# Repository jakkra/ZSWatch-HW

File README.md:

# ZSWatch Hardware

> [!NOTE]
> This is the release branch with tested PCB files.<br>
> For hardware development branch go to [ZSWatch-HW/tree/2.0.6_Dev](https://github.com/jakkra/ZSWatch-HW/tree/2.0.6_Dev).<br>
> For production files pick the [latest run here](https://github.com/jakkra/ZSWatch-HW/actions?query=event%3Apull_request_target) and scroll down to artifacts and pick `Watch`<br>
> Although tested, there may still be unknown issues not yet discovered and ordering ZSWatch PCBs are on your own risk.

## Table of Content

- [ZSWatch Hardware](#zswatch-hardware)
  - [Table of Contents](#table-of-contents)
  - [About](#about)
  - [Dock connector](#dock-connector)
  - [Directory structure](#directory-structure)
  - [Purchasing](#purchasing)
  - [Maintainer](#maintainer)

## About

Hardware repository for the [ZSWatch](https://github.com/jakkra/ZSWatch).

Please check the [wiki](https://github.com/jakkra/ZSWatch/wiki) for more information about the project.

## Dock connector

The pinout for the dock connector is shown below.

<table class="tg">
<thead>
  <tr>
    <th class="tg-0pky"></th>
    <th class="tg-0pky">Pin</th>
    <th class="tg-0pky">Description</th>
  </tr>
</thead>
<tbody>
  <tr>
    <td class="tg-0pky" rowspan="5"></td>
    <td class="tg-0pky">1</td>
    <td class="tg-0pky">VBUS (+5 V)</td>
  </tr>
  <tr>
    <td class="tg-0pky">2</td>
    <td class="tg-0pky">GND</td>
  </tr>
  <tr>
    <td class="tg-0pky">3</td>
    <td class="tg-0pky">SEL</td>
  </tr>
  <tr>
    <td class="tg-0lax">4</td>
    <td class="tg-0lax">D- / SWDIO</td>
  </tr>
  <tr>
    <td class="tg-0lax">5</td>
    <td class="tg-0lax">D+ / SWDCLK</td>
  </tr>
</tbody>
</table>

| SEL  | Function       |
|------|----------------|
|`LOW` | USB            |
|`HIGH`| SWD (Default)  |

## Directory structure

- `cad`: 3D model of the complete PCB
- `docs`: All kinds of project documentation like schematics, BOM, etc.
  - `drawings`: 2D drawings for subcomponents, etc.
  - `images`
- `project`: KiCad project for the PCB

## Purchasing

Please open `ZSWatch-navigate.html` and use the files listed under `purchasing` for ordering a PCB.

## Maintainer

- [Daniel Kampert](mailto:daniel.kameprt@kampis-elektroecke.de)
- [Jakob Krantz](mail@jakobkrantz.se)

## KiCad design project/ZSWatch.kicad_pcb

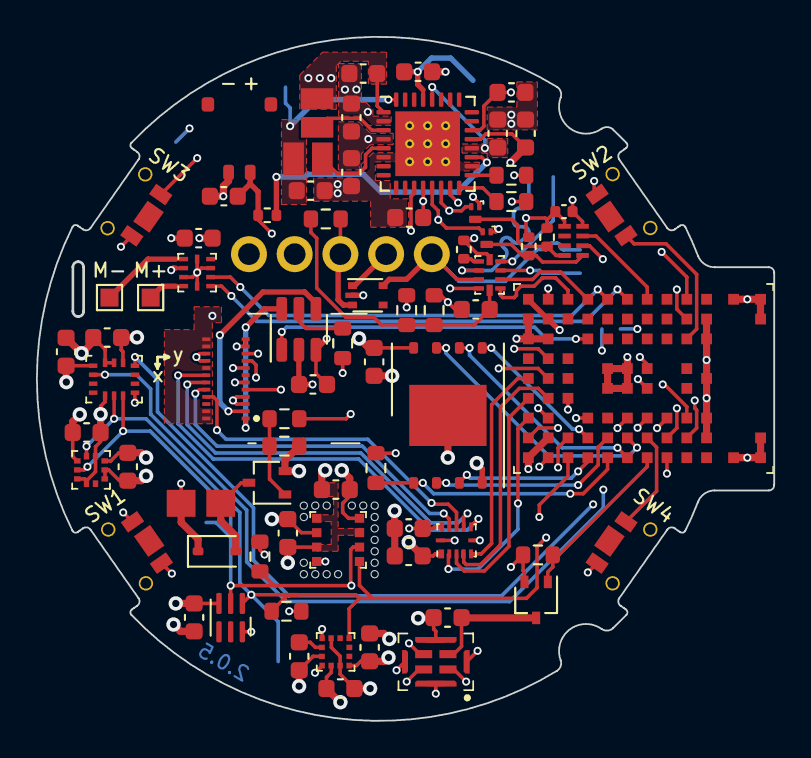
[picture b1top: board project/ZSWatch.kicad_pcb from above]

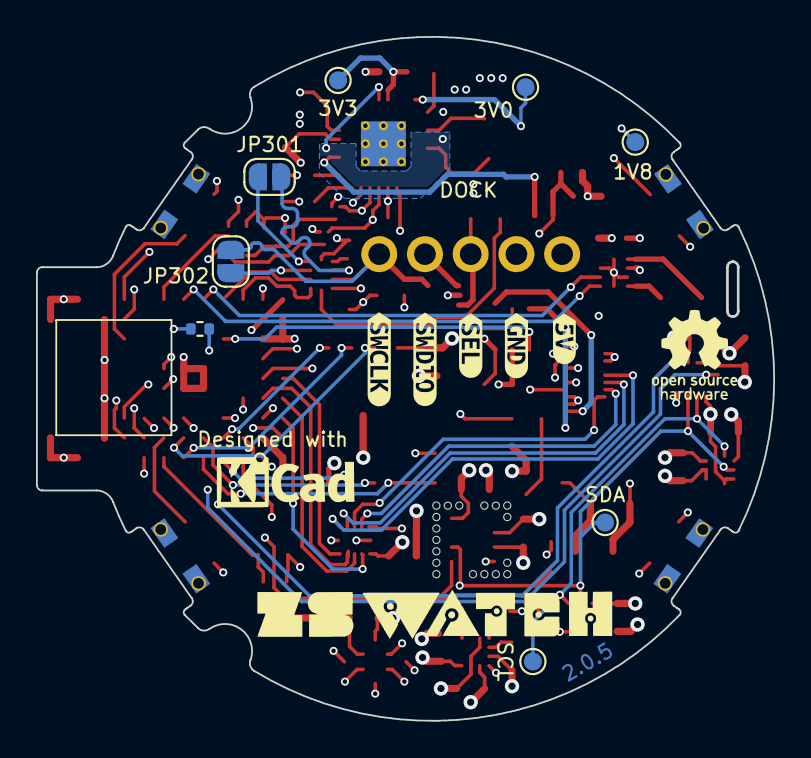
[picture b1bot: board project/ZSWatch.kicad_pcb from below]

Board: 4 copper layers, 41.0 x 38.0 mm, 89 parts (14 on the bottom side), 72 nets.

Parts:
BZ301: Buzzer; CMT-322-65-SMT-TR
C101, C110, C301: 1u; C_0603_1608Metric
C102, C201, C202, C203, C204, C206, C207, C210, C211, C212, C302, C303, C304, C305, C306: 100n; C_0603_1608Metric
C103: 2u2; C_0603_1608Metric
C104, C105, C106, C107, C108, C109, C209: 10u; C_0603_1608Metric
C208: 220n; C_0603_1608Metric
C307: 100n; C_0402_1005Metric
D301: BAS316; D_SOD-323
IC101: nPM1300-QEXX; QFN-32-1EP_5x5mm_P0.5mm_EP3.6x3.6mm_ThermalVias
IC201: APDS-9306-065; Broadcom_DFN-6_2x2mm_P0.65mm
IC202: BMI270; Bosch_LGA-14_3x2.5mm_P0.5mm_LayoutBorder3x4y
IC203: BMP581; Bosch_LGA-10_2x2mm_P0.5mm_ClockwisePinNumbering
IC204: LIS2MDLTR; LGA-12_2x2mm_P0.5mm
IC205: BME688; Bosch_LGA-8_3x3mm_P0.8mm_ClockwisePinNumbering
IC301: ESDALC6V1W5; SOT-665
IC302: FAN5622SX; TSOT-23-6
IC303: MX25U51245GZ4I00; WSON-8-1EP_8x6mm_P1.27mm_EP3.4x4.3mm
IC304: TS3USB221A; UQFN-10_1.55x2.05mm_P0.5mm
IC305: NTS0104GU12; XQFN-12-1.7x2mm_P0.4mm
IC306: DRV2603RUNT; WQFN-10_2x2mm_P0.5mm
IC307: RV-8263-C8
JP301, JP302: SolderJumper-2_P1.3mm_Open_RoundedPad1.0x1.5mm
L101, L102: 2u2; L_0806_2016
M301: NORA-B106
MK201: SPK0641HT4H-1
Q201: DMG1013UW-7; SOT-323_SC-70
Q301: BC817W; SOT-323_SC-70
Q302, Q303: PMZ550UNEYL; SOT-883
R101: 47k; R_0603_1608Metric
R102, R201, R307: 150k; R_0603_1608Metric
R103, R306, R310: 0R; R_0402_1005Metric
R301: 12k; R_0603_1608Metric
R302, R305: 100k; R_0603_1608Metric
R303, R304: 4k7; R_0603_1608Metric
R308: 270R; R_0603_1608Metric
R309, R313: 4k7; R_0402_1005Metric
R311: 180R; R_0603_1608Metric
R312: 100R; R_0603_1608Metric
S301: SW1; TL6340AF160Q_Modified
S302: SW2; TL6340AF160Q_Modified
S303: SW3; TL6340AF160Q_Modified
S304: SW4; TL6340AF160Q_Modified
TP101: 1V8; TestPoint_Pad_D1.0mm
TP102: 3V0; TestPoint_Pad_D1.0mm
TP103: 3V3; TestPoint_Pad_D1.0mm
TP201: SCL; TestPoint_Pad_D1.0mm
TP202: SDA; TestPoint_Pad_D1.0mm
X101: BATTERY; 78171-0002
X301: DOCK; RD90_LZH0230529-004_DJ-5PIN_PH2_54
X302: GC9A01A_CST816S; ER-CON0.4-24P
X303: M+; TestPoint_Pad_1.0x1.0mm
X304: M-; TestPoint_Pad_1.0x1.0mm
kibuzzard-6616D313: G***; kibuzzard-6616D313
kibuzzard-656642B5: G***; kibuzzard-656642B5
kibuzzard-656642E4: G***; kibuzzard-656642E4
kibuzzard-65664337: G***; kibuzzard-65664337
kibuzzard-65664342: G***; kibuzzard-65664342

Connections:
+1V8: C102.1, C107.1, C201.1, C202.1, C203.2, C206.2, C207.1, C209.1, C210.1, C211.1, C212.2, C302.1, C304.1, IC101.1 (VOUT1), IC101.12 (VDDIO), IC201.3 (VDD), IC202.5 (VDDIO), IC202.8 (VDD), IC202.12 (CSB), IC203.1 (VDDIO), IC203.5 (SDO), IC203.6 (CSB), IC203.10 (VDD), IC204.3 (CS), IC204.9 (VDD), IC204.10 (VDDIO), IC205.2 (CSB), IC205.6 (VDDIO), IC205.8 (VDD), IC303.8 (VCC), IC305.1 (VCCA), L102.1, M301.A7 (VDD), M301.A8 (VDDH), M301.B7 (VDD), MK201.3 (SEL), Q201.2 (S), Q302.1 (G), Q303.1 (G), R201.2, R302.1, R303.1, R304.1, TP101.1, X302.11 (VDDIO), X302.12 (VDDIO)
+3V0: BZ301.1 (+), C105.1, D301.1 (K), IC101.32 (VOUT2), L101.1, TP102.1
/MCU/BMI270-INT1: IC202.4 (INT1), M301.G5 (P1.08)
/MCU/BMI270-INT2: IC202.9 (INT2), M301.G4 (P1.04)
/MCU/LIS2MDL-INT: IC204.7 (INT/DRDY), M301.H1 (P0.24)
/MCU/MIC-CLK: M301.F3 (P0.19), MK201.2 (CLK)
/MCU/MIC-DATA: M301.G3 (P0.25/AIN4), MK201.1 (DATA)
/MCU/MIC-EN: M301.G1 (P1.06), Q201.1 (G), R201.1
/MCU/PMIC-INT: IC101.11 (GPIO4), M301.J8 (P0.28/AIN7)
/MCU/SENSOR-SCL: IC101.14 (SCL), IC201.1 (SCL), IC202.13 (SCK), IC203.2 (SCK), IC204.1 (SCL/SPC), IC205.4 (SCK), M301.D3 (P0.07/AIN3), Q302.2 (S), R304.2, TP201.1
/MCU/SENSOR-SDA: IC101.13 (SDA), IC201.2 (SDA), IC202.14 (SDI), IC203.4 (SDI), IC204.4 (SDA/SDI/SDO), IC205.3 (SDI), M301.C1 (P0.10/TRACEDATA[1]), Q303.2 (S), R303.2, TP202.1
/MCU/VBAT: C103.1, C307.1, IC307.5 (VDD), R103.1, R309.1, R313.1, X101.1
/MCU/VBUS-MCU: C110.1, IC101.22 (VBUSOUT), M301.B9 (VBUS), R312.1
/MCU/VDD-Display: C108.1, C301.2, C305.1, IC101.29 (LSOUT1/VOUTLDO1), IC302.3 (VIN), IC305.11 (VCCB), TP103.1, X302.13 (VDD), X302.14 (VDD), X302.17 (CTP-VDD), X302.23 (LEDA2), X302.24 (LEDA1)
/MCU/VSYS: C104.1, C106.1, C109.1, C306.1, IC101.4 (PVDD), IC101.20 (VSYS), IC101.28 (LSIN1/VINLDO1), IC306.7 (VDD)
/MCU/V_SWITCH: C303.1, IC304.10 (VDD), R305.1, R308.1, R312.2
BTN-1: M301.H3 (P0.27/AIN6), S301.1
BTN-2: M301.J7 (P1.10), S302.2
BTN-3: IC101.15 (SHPHLD), M301.J9 (P0.31), S303.2
BTN-4: M301.G2 (P0.26/AIN5), S304.1
BUZZER: M301.B6 (P0.01/XL2), R311.1
DISPLAY-BLK: IC302.1 (CTRL), M301.D7 (P0.23)
DISPLAY-CLK: M301.B1 (P0.08/TRACEDATA[3]), X302.8 (SCL)
DISPLAY-CS: M301.A2 (P0.12/TRACECLK), X302.9 (CS)
DISPLAY-DATA: M301.C2 (P0.09/TRACEDATA[2]), X302.6 (SDI/SDA)
DISPLAY-DC: M301.B3 (P0.11/TRACEDATA[0]), X302.5 (RS/DC)
DISPLAY-EN: IC305.12 (OE), M301.C4 (P1.01)
DISPLAY-RST: M301.B5 (P0.03/NFC2), X302.10 (RESET)
D_N/SWDIO: IC301.1 (I/01), IC304.7 (D-), JP301.1 (A), X301.2
D_P/SWDCLK: IC301.5 (I/04), IC304.8 (D+), JP302.1 (A), X301.1
GND: C101.2, C102.2, C103.2, C104.2, C105.2, C106.2, C107.2, C108.2, C109.2, C110.2, C201.2, C202.2, C203.1, C204.2, C206.1, C207.2, C208.2, C209.2, C210.2, C211.2, C212.1, C301.1, C302.2, C303.2, C304.2, C305.2, C306.2, C307.2, IC101.2 (PVSS1), IC101.6 (PVSS2), IC101.18 (NTC), IC101.33 (AVSS), IC201.6 (GND), IC202.1 (SDO), IC202.6 (GND), IC202.7 (GND), IC203.3 (GND), IC203.8 (GND), IC203.9 (GND), IC204.6 (GND), IC204.8 (GND), IC205.1 (GND), IC205.5 (SDO), IC205.7 (GND), IC301.2 (GND), IC302.2 (GND), IC303.4 (GND), IC303.9 (EP), IC304.5 (GND), IC305.6 (GND), IC306.3 (LRA/~ERM), IC306.5 (GND), IC306.8 (GND), IC306.10 (GND), IC307.2 (CLKOE), IC307.4 (GND), M301.A1 (GND), M301.A9 (GND), M301.B2 (GND), M301.B8 (GND), M301.E4 (GND), M301.E5 (GND), M301.F4 (GND), M301.F5 (GND), M301.K2 (GND), M301.K3 (GND), M301.K5 (GND), M301.K7 (GND), M301.K8 (GND), M301.L1 (GND), M301.L9 (GND), M301.M1 (GND), M301.M2 (GND), M301.M8 (GND), M301.M9 (GND), MK201.5 (GND), MK201.6 (GND), MK201.7 (GND), MK201.8 (GND), Q301.2 (E), R101.1, R102.1, R301.1, R307.1, R308.2, R310.2, S301.2, S302.1, S303.1, S304.2, X101.2, X301.4, X302.3 (GND), X302.4 (GND), X302.15 (GND), X302.16 (GND)
LEDK1: IC302.6 (LED1), X302.1 (LEDK-1)
LEDK2: IC302.4 (LED2), X302.2 (LEDK-2)
unnamed: BZ301.2 (-), D301.2 (A), Q301.3 (C)
unnamed: IC101.3 (SW1), L102.2
unnamed: IC101.5 (SW2), L101.2
unnamed: IC101.19 (VBAT), R103.2
unnamed: IC101.17 (VSET1), R101.2
unnamed: IC101.16 (VSET2), R102.2
unnamed: C208.1, IC204.5 (C1)
unnamed: IC302.5 (ISET), R301.2
unnamed: IC304.6 (~OE), R310.1
unnamed: IC305.10 (B1), X302.20 (CTP-SCL)
unnamed: IC305.9 (B2), X302.21 (CTP-INT)
unnamed: IC305.8 (B3), X302.19 (CTP-SDA)
unnamed: IC305.7 (B4), X302.18 (CTP-RST)
unnamed: IC306.9 (OUT+), X303.1
unnamed: IC306.6 (OUT-), X304.1
unnamed: IC307.8 (SCL), Q302.3 (D), R313.2
unnamed: IC307.1 (SDA), Q303.3 (D), R309.2
unnamed: C204.1, MK201.4 (VDD), Q201.3 (D)
unnamed: Q301.1 (B), R307.2, R311.2
QSPI-CLK: IC303.6 (SCK), M301.F1 (P0.17/QSPI_CLK)
QSPI-CS: IC303.1 (~CS), M301.E1 (P0.18/QSPI_CS), R302.2
QSPI-IO0: IC303.5 (SI(I/O0)), M301.D2 (P0.13/QSPI[0])
QSPI-IO1: IC303.2 (SO(I/O1)), M301.E2 (P0.14/QSPI[1])
QSPI-IO2: IC303.3 (~WP(I/O2)), M301.D1 (P0.15/QSPI[2])
QSPI-IO3: IC303.7 (~HOLD(I/O3)), M301.F2 (P0.16/QSPI[3])
RESETn: M301.J3 (~RESET), R306.2
SEL-SWD: IC301.3 (I/02), IC304.9 (S), R305.2, R306.1, X301.3
SWDCLK: IC304.3 (2D+), JP302.2 (B), M301.J2 (SWDCLK)
SWDIO: IC304.4 (2D-), JP301.2 (B), M301.H2 (SWDIO)
TOUCH-INT: IC305.3 (A2), M301.A4 (P1.00)
TOUCH-RST: IC305.5 (A4), M301.A5 (P0.20)
TOUCH-SCL: IC305.2 (A1), M301.A3 (P1.03/I2C)
TOUCH-SDA: IC305.4 (A3), M301.B4 (P1.02/I2C)
USB-D_N: IC304.2 (1D-), M301.D9 (D-)
USB-D_P: IC304.1 (1D+), M301.C9 (D+)
VBUS: C101.1, IC101.21 (VBUS), X301.5
VIB-EN: IC306.1 (EN), M301.F9 (P1.15)
VIB-PWM: IC306.2 (PWM), M301.E9 (P1.05)
nRTC-INT: IC307.3 (~INT), M301.G9 (P1.13)

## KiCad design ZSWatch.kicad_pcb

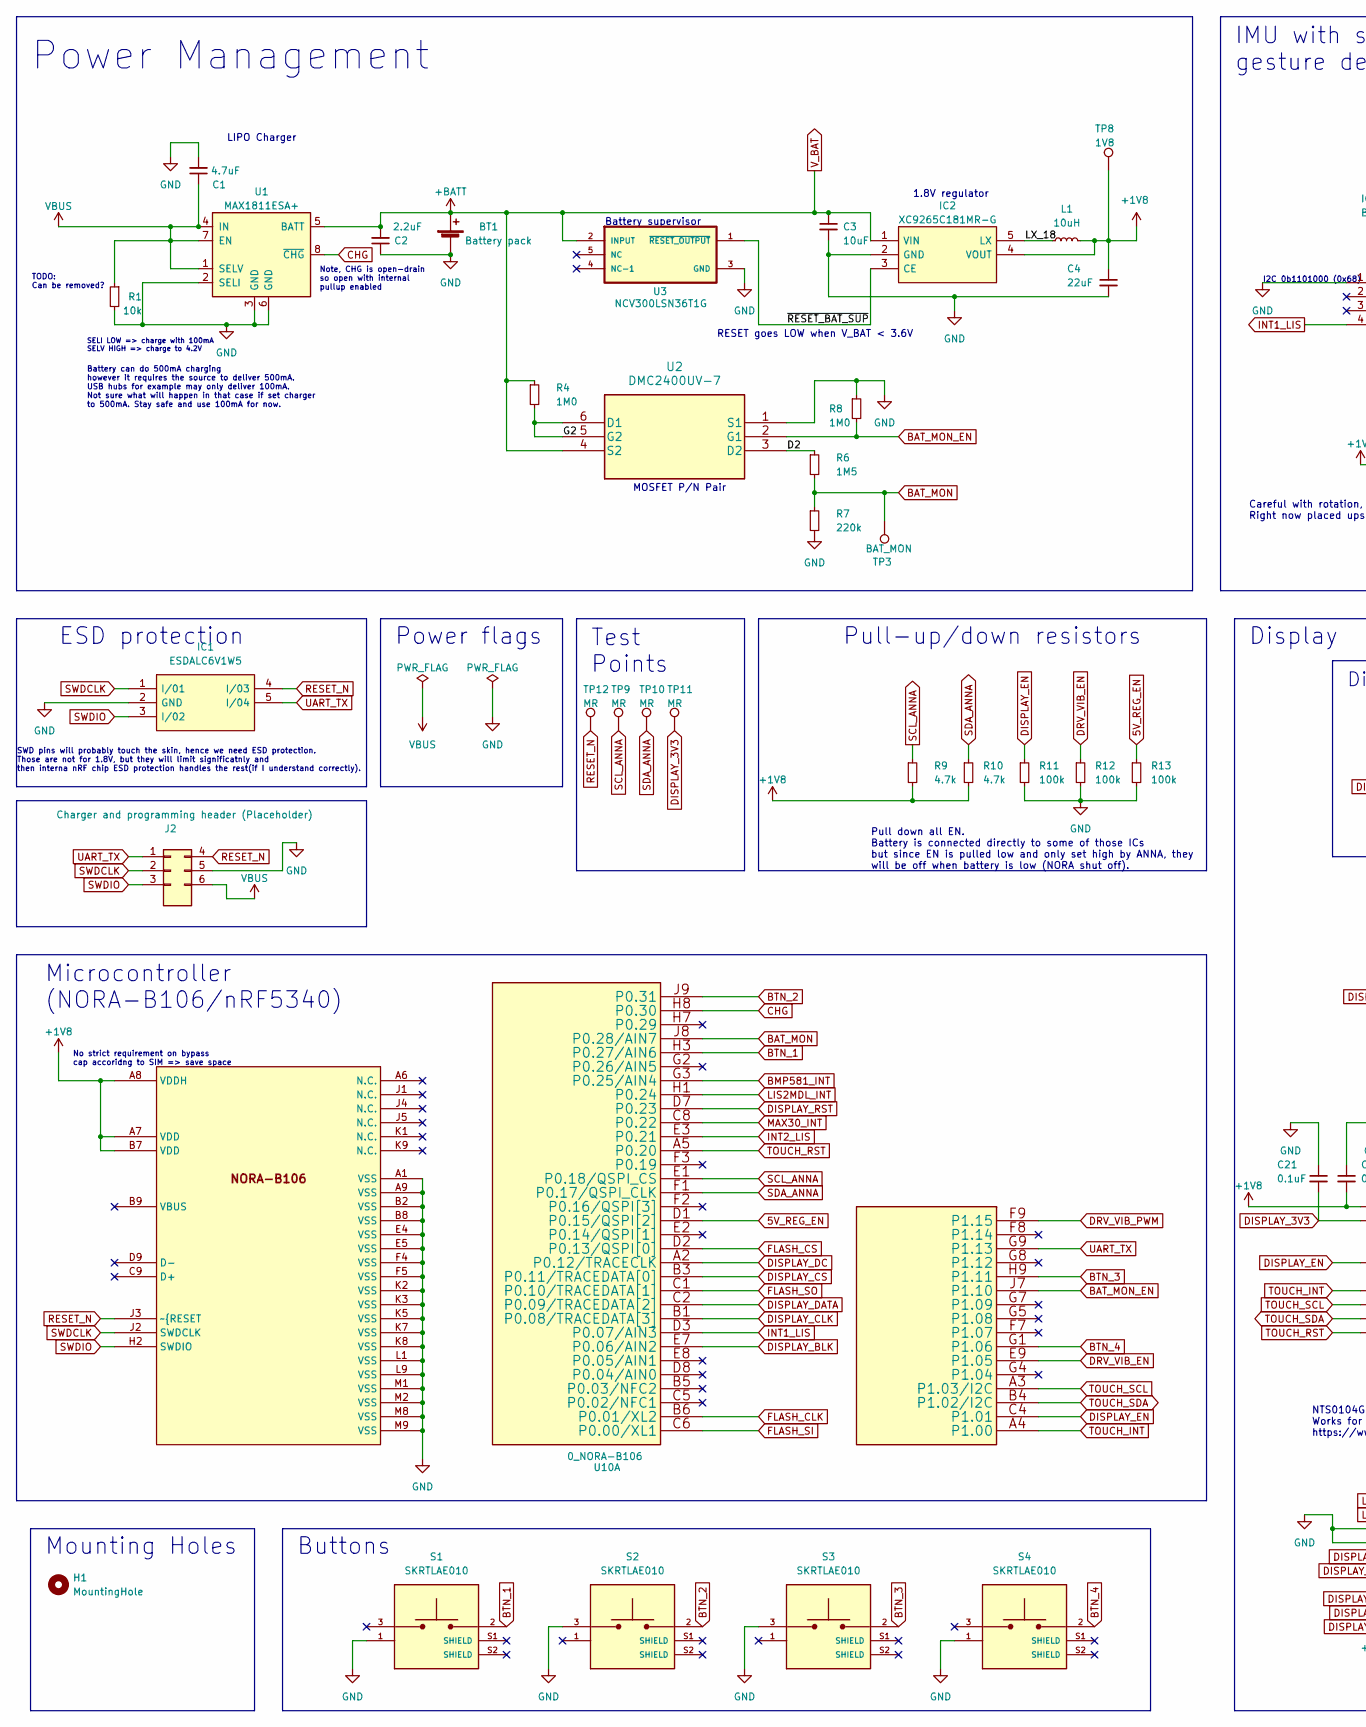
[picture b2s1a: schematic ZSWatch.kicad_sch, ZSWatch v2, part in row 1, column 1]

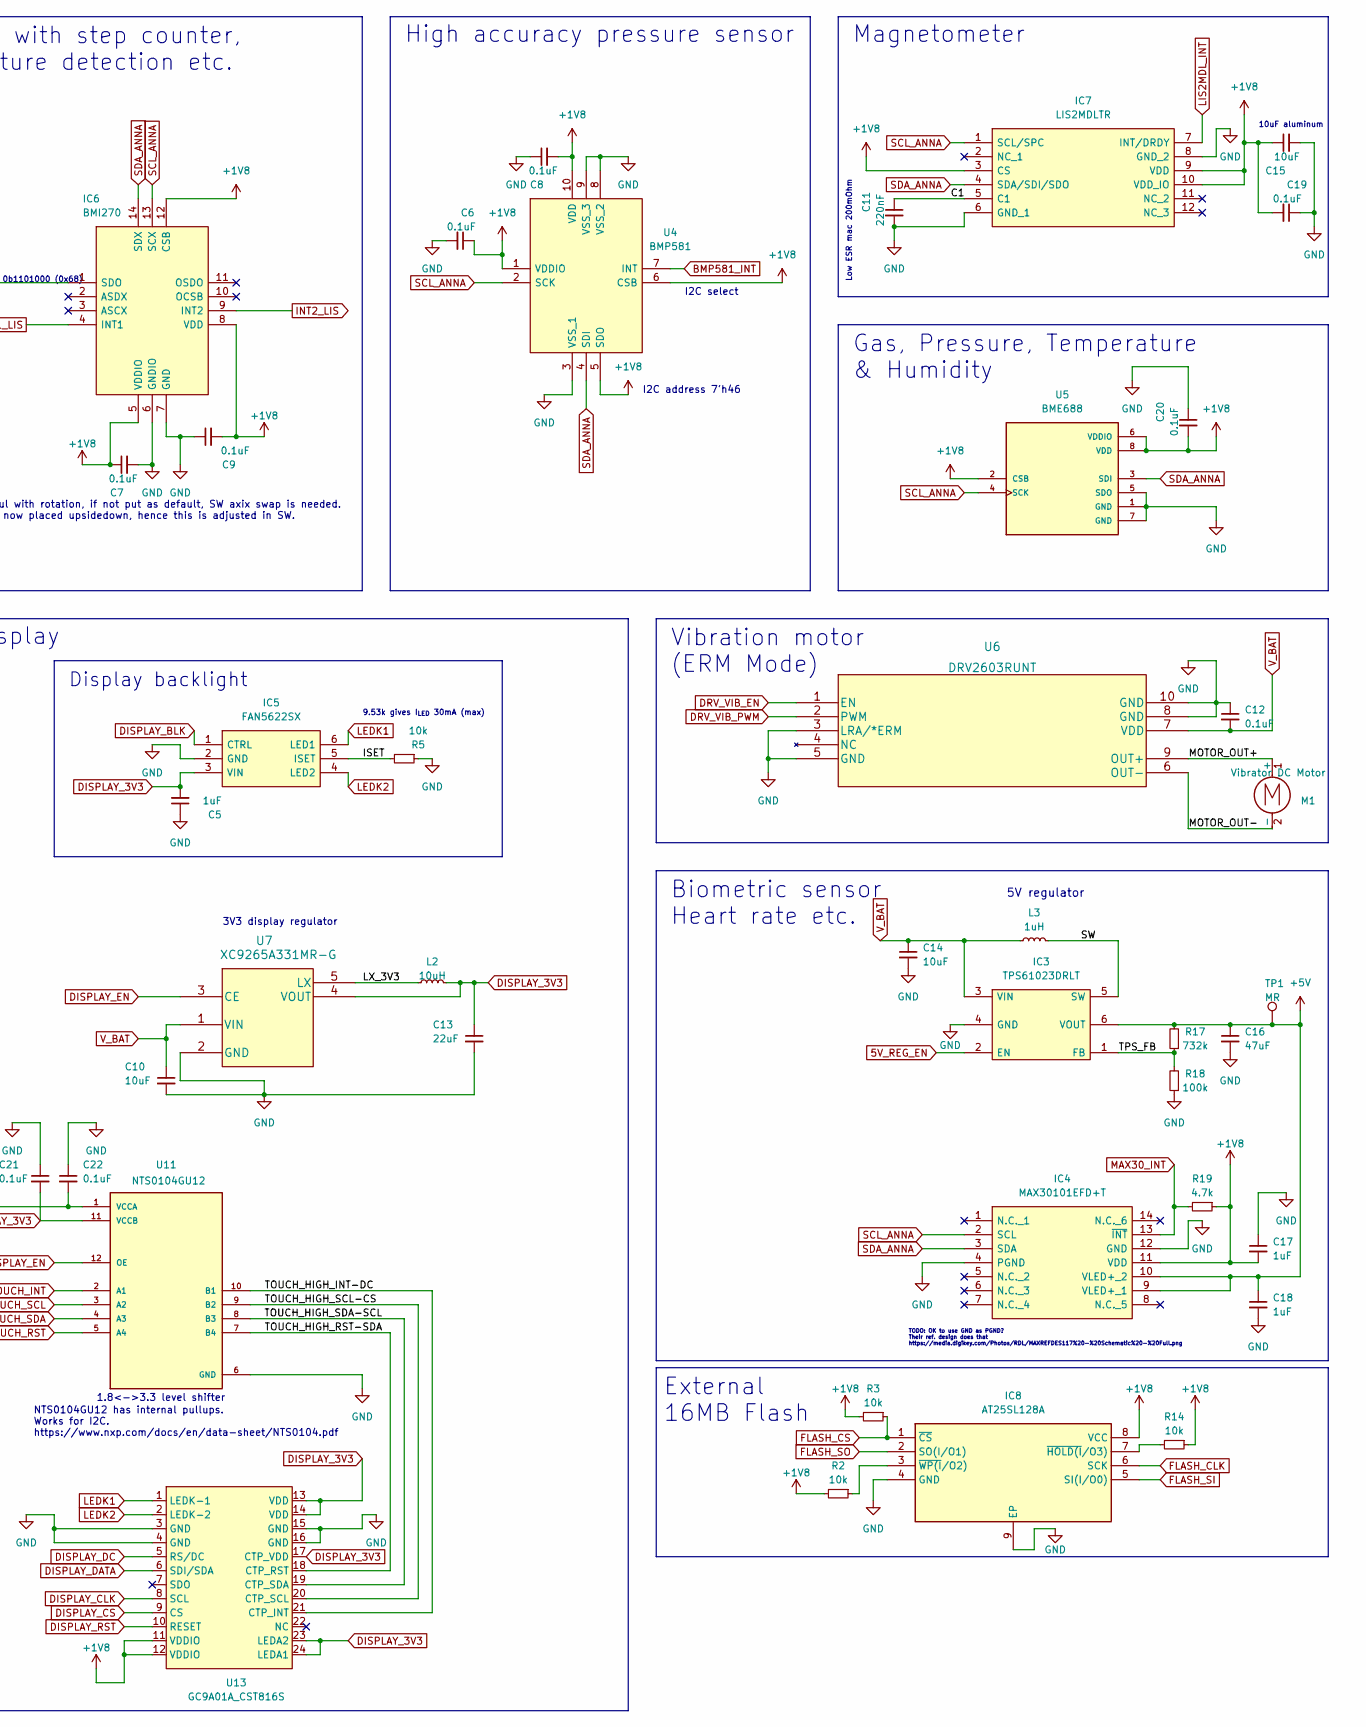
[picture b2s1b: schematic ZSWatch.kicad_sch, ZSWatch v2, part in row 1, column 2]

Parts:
BT1: Battery pack; SolderWire-0.1sqmm_1x02_P3.6mm_D0.4mm_OD1mm
C1: 4.7uF; C_0603_1608Metric
C2: 2.2uF; C_0603_1608Metric
C3, C10, C14, C15: 10uF; C_0603_1608Metric
C4, C13: 22uF; C_0603_1608Metric
C5, C17, C18: 1uF; C_0603_1608Metric
C6, C7, C8, C9, C12, C19, C20, C21, C22: 0.1uF; C_0603_1608Metric
C11: 220nF; C_0603_1608Metric
C16: 47uF; C_0603_1608Metric
H1: MountingHole; MountingHole_3.5mm_Pad_Via
IC1: ESDALC6V1W5; SOT65P210X110-5L; Mouser Part Number 511-ESDALC6V1W5
IC2: XC9265C181MR-G; SOT95P280X130-5N; Mouser Part Number 865-XC9265C181MR-G
IC3: TPS61023DRLT; SOTFL50P160X60-6N; Mouser Part Number 595-TPS61023DRLT
IC4: MAX30101EFD+T; 14-LEAD-OESIP; Mouser Part Number 700-MAX30101EFD+T
IC5: FAN5622SX; SOT95P280X110-6N; Mouser Part Number 512-FAN5622SX
IC6: BMI270; QFN50P300X250X87-14N; Mouser Part Number 262-BMI270
IC7: LIS2MDLTR; LGA-12; Mouser Part Number 511-LIS2MDLTR
IC8: AT25SL128A; SON127P600X500X60-9N-D; Manufacturer_Part_Number 988-AT25SL128A-MHE-T; Mouser Part Number 988-AT25SL128A-MHE-T
J2: Charger and programming header (Placeholder); rtlecs-6-pin-2-54
L1, L2: 10uH; L_0603_1608Metric
L3: 1uH; L_0603_1608Metric
M1: Vibrator DC Motor; TestPoint_2Pads_Pitch2.54mm_Drill0.8mm
R1, R5, R14: 10k; R_0603_1608Metric
R2, R3: 10k; R_0402_1005Metric
R4, R8: 1M0; R_0603_1608Metric
R6: 1M5; R_0603_1608Metric
R7: 220k; R_0603_1608Metric
R9, R10, R19: 4.7k; R_0603_1608Metric
R11, R12, R13, R18: 100k; R_0603_1608Metric
R17: 732k; R_0603_1608Metric
S1, S2, S3, S4: SKRTLAE010; SW_SKRTLAE010; PARTREV --
TP1, TP9, TP10, TP11, TP12: MR; TestPoint_Pad_D1.0mm
TP3: BAT_MON; TestPoint_Pad_D1.0mm
TP8: 1V8; TestPoint_Pad_D1.0mm
U1: MAX1811ESA+; SOIC127P600X175-8N
U2: DMC2400UV-7
U3: NCV300LSN36T1G; SOT95P275X110-5N
U4: BMP581; Mouser Part Number 262-BMP581
U5: BME688; IC_BME688; PARTREV 1.0
U6: DRV2603RUNT
U7: XC9265A331MR-G; SOT95P280X130-5N
U10: 0_NORA-B106; NORA_LGA82R_1430X1040X180_ANT; MANUFACTURER P/N NORA-B106-00B
U11: NTS0104GU12; HPA01164RUTR; PARTREV 4210580/C 06/12
U13: GC9A01A_CST816S; ER-24F24-04

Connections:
5V_REG_EN: IC3.2 (EN), R13.1, U10.D1 (P0.15/QSPI[2])
+5V: C16.1, C18.1, IC3.6 (VOUT), IC4.9 (VLED+_1), IC4.10 (VLED+_2), R17.2, TP1.1
/C1: C11.1, IC7.5 (C1)
/D2: R6.1, U2.3 (D2)
/G2: R4.2, U2.5 (G2), U2.6 (D1)
/ISET: IC5.5 (ISET), R5.2
/LX_3V3: L2.1, U7.5 (LX)
/LX_18: IC2.5 (LX), L1.1
/MOTOR_OUT+: M1.1 (+), U6.9 (OUT+)
/MOTOR_OUT-: M1.2 (-), U6.6 (OUT-)
/SW: IC3.5 (SW), L3.2
/TOUCH_HIGH_INT-DC: U11.10 (B1), U13.21 (CTP_INT)
/TOUCH_HIGH_RST-SDA: U11.7 (B4), U13.18 (CTP_RST)
/TOUCH_HIGH_SCL-CS: U11.9 (B2), U13.20 (CTP_SCL)
/TOUCH_HIGH_SDA-SCL: U11.8 (B3), U13.19 (CTP_SDA)
/TPS_FB: IC3.1 (FB), R17.1, R18.2
/~RESET_BAT_SUP: IC2.3 (CE), U3.1 (~RESET_OUTPUT)
BAT_MON: R6.2, R7.1, TP3.1, U10.J8 (P0.28/AIN7)
BAT_MON_EN: R8.2, U2.2 (G1), U10.J7 (P1.10)
BMP581_INT: U4.7 (INT), U10.G3 (P0.25/AIN4)
BTN_1: S1.2, U10.H3 (P0.27/AIN6)
BTN_2: S2.2, U10.J9 (P0.31)
BTN_3: S3.2, U10.H9 (P1.11)
BTN_4: S4.2, U10.G1 (P1.06)
CHG: U1.8 (~CHG), U10.H8 (P0.30)
DISPLAY_3V3: C5.2, C13.1, C21.2, IC5.3 (VIN), L2.2, TP11.1, U7.4 (VOUT), U11.11 (VCCB), U13.13 (VDD), U13.14 (VDD), U13.17 (CTP_VDD), U13.23 (LEDA2), U13.24 (LEDA1)
DISPLAY_BLK: IC5.1 (CTRL), U10.E7 (P0.06/AIN2)
DISPLAY_CLK: U10.B1 (P0.08/TRACEDATA[3]), U13.8 (SCL)
DISPLAY_CS: U10.B3 (P0.11/TRACEDATA[0]), U13.9 (CS)
DISPLAY_DATA: U10.C2 (P0.09/TRACEDATA[2]), U13.6 (SDI/SDA)
DISPLAY_DC: U10.A2 (P0.12/TRACECLK), U13.5 (RS/DC)
DISPLAY_EN: R11.1, U7.3 (CE), U10.C4 (P1.01), U11.12 (OE)
DISPLAY_RST: U10.D7 (P0.23), U13.10 (RESET)
DRV_VIB_EN: R12.1, U6.1 (EN), U10.E9 (P1.05)
DRV_VIB_PWM: U6.2 (PWM), U10.F9 (P1.15)
FLASH_CLK: IC8.6 (SCK), U10.B6 (P0.01/XL2)
FLASH_SI: IC8.5 (SI(I/O0)), U10.C6 (P0.00/XL1)
FLASH_SO: IC8.2 (SO(I/O1)), U10.C1 (P0.10/TRACEDATA[1])
GND: BT1.2 (-), C1.2, C2.1, C3.2, C4.2, C5.1, C6.2, C7.2, C8.1, C9.1, C10.2, C11.2, C12.1, C13.2, C14.2, C15.2, C16.2, C17.1, C18.2, C19.1, C20.1, C21.1, C22.1, IC1.2 (GND), IC2.2 (GND), IC3.4 (GND), IC4.4 (PGND), IC4.12 (GND), IC5.2 (GND), IC6.1 (SDO), IC6.6 (GNDIO), IC6.7 (GND), IC7.6 (GND_1), IC7.8 (GND_2), IC8.4 (GND), IC8.9 (EP), J2.5, R1.2, R5.1, R7.2, R8.1, R11.2, R12.2, R13.2, R18.1, S1.1, S2.3, S3.3, S4.1, U1.2 (SELI), U1.3 (GND), U1.6 (GND), U2.1 (S1), U3.3 (GND), U4.3 (VSS_1), U4.8 (VSS_2), U4.9 (VSS_3), U5.1 (GND), U5.5 (SDO), U5.7 (GND), U6.3 (LRA/*ERM), U6.5 (GND), U6.8 (GND), U6.10 (GND), U7.2 (GND), U10.A1 (VSS), U10.A9 (VSS), U10.B2 (VSS), U10.B8 (VSS), U10.E4 (VSS), U10.E5 (VSS), U10.F4 (VSS), U10.F5 (VSS), U10.K2 (VSS), U10.K3 (VSS), U10.K5 (VSS), U10.K7 (VSS), U10.K8 (VSS), U10.L1 (VSS), U10.L9 (VSS), U10.M1 (VSS), U10.M2 (VSS), U10.M8 (VSS), U10.M9 (VSS), U11.6 (GND), U13.3 (GND), U13.4 (GND), U13.15 (GND), U13.16 (GND)
INT1_LIS: IC6.4 (INT1), U10.D3 (P0.07/AIN3)
INT2_LIS: IC6.9 (INT2), U10.E3 (P0.21)
LEDK1: IC5.6 (LED1), U13.1 (LEDK-1)
LEDK2: IC5.4 (LED2), U13.2 (LEDK-2)
LIS2MDL_INT: IC7.7 (INT/DRDY), U10.H1 (P0.24)
MAX30_INT: IC4.13 (~INT), R19.2, U10.C8 (P0.22)
unnamed: IC8.3 (~WP(I/O2)), R2.1
RESET_N: IC1.4 (I/03), J2.4, TP12.1, U10.J3 (~{RESET)
SCL_ANNA: IC4.2 (SCL), IC6.13 (SCX), IC7.1 (SCL/SPC), R9.1, TP9.1, U4.2 (SCK), U5.4 (SCK), U10.E1 (P0.18/QSPI_CS)
SDA_ANNA: IC4.3 (SDA), IC6.14 (SDX), IC7.4 (SDA/SDI/SDO), R10.1, TP10.1, U4.4 (SDI), U5.3 (SDI), U10.F1 (P0.17/QSPI_CLK)
SWDCLK: IC1.1 (I/01), J2.2, U10.J2 (SWDCLK)
SWDIO: IC1.3 (I/02), J2.3, U10.H2 (SWDIO)
TOUCH_INT: U10.A4 (P1.00), U11.2 (A1)
TOUCH_RST: U10.A5 (P0.20), U11.5 (A4)
TOUCH_SCL: U10.A3 (P1.03/I2C), U11.3 (A2)
TOUCH_SDA: U10.B4 (P1.02/I2C), U11.4 (A3)
UART_TX: IC1.5 (I/04), J2.1, U10.G9 (P1.13)
VBUS: C1.1, J2.6, R1.1, U1.1 (SELV), U1.4 (IN), U1.7 (EN)
V_BAT: BT1.1 (+), C2.2, C3.1, C10.1, C12.2, C14.1, IC2.1 (VIN), IC3.3 (VIN), L3.1, R4.1, U1.5 (BATT), U2.4 (S2), U3.2 (INPUT), U6.7 (VDD), U7.1 (VIN)

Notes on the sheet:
Test Points
Display backlight
Battery can do 500mA charging however it requires the source to deliver 500mA. USB hubs for example may only deliver 100mA. Not sure what will happen in that case if set charger to 500mA. Stay safe and use 100mA for now.
1.8<->3.3 level shifter
I2C select
Biometric sensor Heart rate etc.
Gas, Pressure, Temperature & Humidity
High accuracy pressure sensor
3V3 display regulator
Pull-up/down resistors
MOSFET P/N Pair
Power Management
SELI LOW => charge with 100mA SELV HIGH => charge to 4.2V
Battery supervisor
RESET goes LOW when V_BAT < 3.6V
I2C address 7'h46
Low ESR mac 200mOhm
_{I2C 0b1101000 (0x68)}
NTS0104GU12 has internal pullups. Works for I2C. https://www.nxp.com/docs/en/data-sheet/NTS0104.pdf
TODO: Can be removed?
Buttons
Microcontroller (NORA-B106/nRF5340)
TODO: OK to use GND as PGND? Their ref. design does that https://media.digikey.com/Photos/RDL/MAXREFDES117%20-%20Schematic%20-%20Full.png
Note, CHG is open-drain so open with internal pullup enabled
No strict requirement on bypass cap accoridng to SIM => save space
Power flags
9.53k gives I_{LED} 30mA (max)
Magnetometer
SWD pins will probably touch the skin, hence we need ESD protection. Those are not for 1.8V, but they will limit significatnly and then interna nRF chip ESD protection handles the rest(if I understand correctly).
Pull down all EN. Battery is connected directly to some of those ICs but since EN is pulled low and only set high by ANNA, they will be off when battery is low (NORA shut off).
Careful with rotation, if not put as default, SW axix swap is needed. Right now placed upsidedown, hence this is adjusted in SW.
IMU with step counter, gesture detection etc.
LIPO Charger
5V regulator
External 16MB Flash
ESD protection
Vibration motor (ERM Mode)
Mounting Holes
Display
10uF aluminum

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
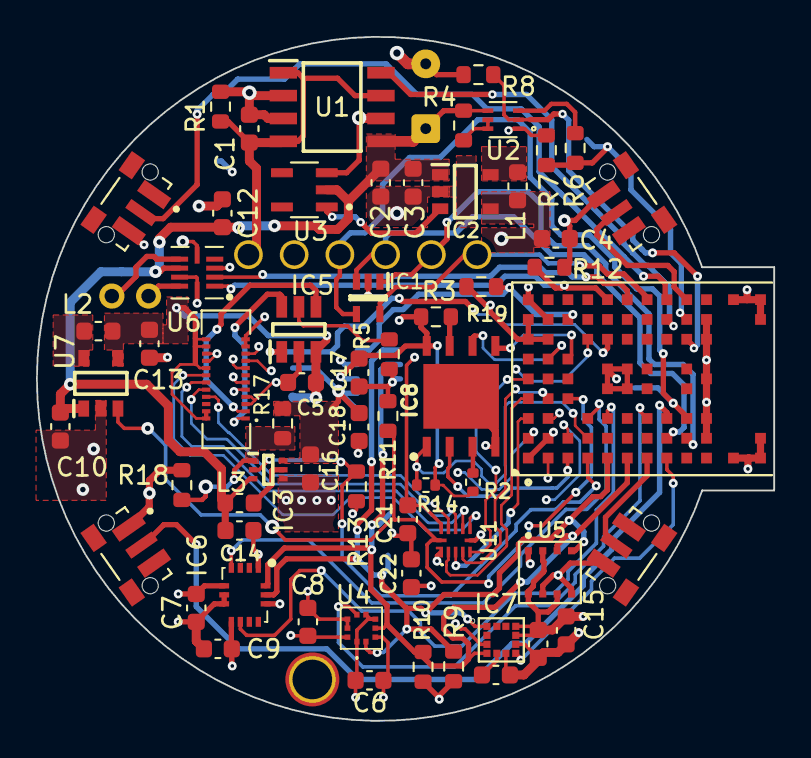
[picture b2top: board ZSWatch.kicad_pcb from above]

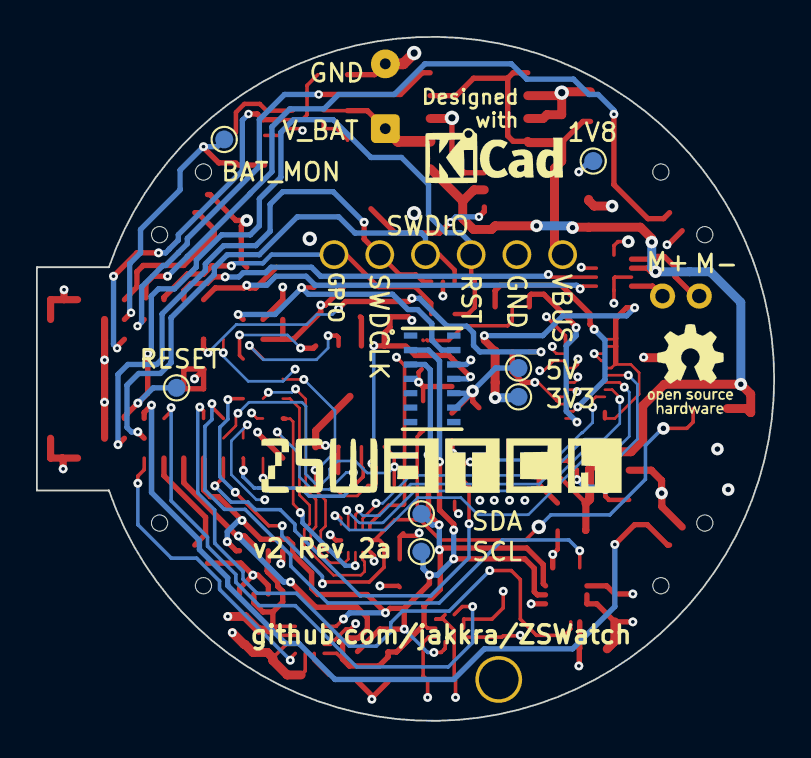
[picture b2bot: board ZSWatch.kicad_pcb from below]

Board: 4 copper layers, 41.0 x 38.0 mm, 74 parts (9 on the bottom side), 61 nets.

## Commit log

2023-08-21 Moved ZSWatch PCB v2.0.0 from main ZSWatch repo to its own.
2023-08-21 Restructure project, add hardware release 2.0.3
2023-08-23 Add magnet contact instead of pin header for the dock connector, create new manufacturing data and sync them with PCBWay BOM, update README
2023-09-25 PCB and documentation update
    - Update README
    - Add values to PCB silkscreen
    - Add "+" and "-" marker for battery contact
    - Add magnet contact instead of pin header for the dock connector
    - Create new manufacturing data and sync them with PCBWay BOM
    - Add Ref_Top
2023-09-25 Add release date, finalize production files for the release
2023-09-29 - Change PCB thickness to 1 mm
2023-09-30 - Add blue color to PCB settings - Add surface option to PCB settings
2023-10-01 - Streamline documentation and production files - Ready to merge
2023-10-21 Case: Add CAD and 3D printing files for the case.
2023-10-23 - Add correct manufacturer part number for display connector in BOM - Add "Do not place" instruction to dock connector in BOM
2023-10-25 - Fix wrong part number for 10 uH inductors because the old part was a 1 uH inductor.
2023-10-28 Use QSPI for flash.
2023-10-29 - Update libraries to the latest version - Set correct version number in CHANGELOG - Cosmetic changes - Add new production files
2023-10-29 Add warning regarding external flash not using QSPI in v3 HW.
2023-11-17 Change quantity for 100k resistors to 3 instead of 5
2023-11-28 - Add QR code library with link to the project - Change ISET resistor to 12k - Replace light sensor footprint with a version from our KiCad library - Rename the inner copper layers - Add KiBot file f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
2023-11-28 v4 design validated, remove warning in README.
2023-12-02 - Add QR code library with link to the project - Change ISET resistor to 12k - Replace light sensor footprint with a version from our KiCad library - Rename the inner copper layers - Add KiBot file f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
2023-12-13 Update case CAD files.
2023-12-27 - Add QR code library with link to the project - Change ISET resistor to 12k - Replace light sensor footprint with a version from our KiCad library - Rename the inner copper layers - Add KiBot file f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
2023-12-27 - Add CI/CD pipelines for documentation
2023-12-27 - Remove environment variables from Kibot configuration
2024-01-11 - Remove S1, S2 and S4 from Sensor variant - Remove microphone from Sensor variant - Update symbols - Add missing supply chain documentation - Update KiBot template to the newest version
2024-01-21 Fix soldermask in switches footprint. Fixes https://github.com/jakkra/ZSWatch-HW/issues/11
    PCBWay did always automatically fix this issue, until once they didn't
    and this issue occurred.
2024-01-21 Add reference images of assembled PCB in Production files Others.zip.
2024-01-21 Decrease size of production zip Other.zip.
    Due to file size limit at PCBWay.
2024-01-22 Update README.md
    - Add CI/CD badge
2024-01-26 - Set value for current measurement jumper
2024-01-28 - Remove old documentation - Update libraries - Rename signals - Update CHANGELOG
2024-01-30 Replace VBAT with VBUSOUT
2024-01-30 Update footprints
2024-02-05 Dock-Connector.drawio eingefügt
2024-02-05 Update README, replace current measurement jumper with 0402 resistor on TOP side, update footprints and symbols
2024-02-05 Update zswatch.kibot.yaml
    Fix wrong layer name for inner layer 2
2024-02-05 Add index page and datasheet downloader to KiBot configuration
2024-02-05 Replace I2C mic with SPK0641HT4H-1
2024-02-05 Fix documentation issues
2024-02-06 - Update mic footprint
2024-02-06 Some cosmetic adjustments
2024-02-06 Rename buttons
2024-02-07 Update README.md
    Fix wrong link in license badge
2024-02-07 Add image from CI/CD action
2024-02-17 Add Bus nets
2024-02-19 - Add comment for PCBWay stackup to layout - Clean up layout
2024-02-19 - Remove dock connector from BOM and P&P data - Add manufacturer data for display connector
2024-02-20 Remove color information for soldermask from project
2024-02-20 Add perforation for BME688 sensor
2024-02-20 Add blue color for PCB again, leave it as not specified in the stackup
2024-02-23 Change drill size for BME688 thermal isolation to 0.4 mm
2024-03-01 Update library paths, fix wrong supply voltage for vibration motor (VSys instead VBusOut)
2024-03-03 Fix wrong file extension for image
2024-03-10 - Add create images directory to CI/CD - Add QR-Code image
2024-03-26 Fix wrong value and datasheet for microphone
2024-03-26 Replace QR code with area for QR code
2024-04-11 - Replace flash with MX25L51245GZ2I - Replace bridge resistors for SWD / USB switch with jumpers - Fix missing datasheets, update documentation - Fix wrong reset label at the dock connector - Add new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
2024-04-26 Fix reference sizes in Ref view
2024-04-28 - Remove pull up option for SEL pin - Add voltage divider as power supply for the USB / SWD switch - Add pull-down resistor for buzzer transistor
2024-05-08 - Add RV-8263-C8 - Update CHANGELOG
2024-05-26 - Set pull up resistor on SEL pin to NA - Remove old PCB image from docs
2024-05-27 Remove USB jumpers from BOM, rename suffix for inner layer gerber files
2024-07-16 Fix different manufacturing issues
2024-07-17 Remove old folder not used anymore.
2024-07-18 Bring back production directory with images for ordering at PCBWay, prevent File exists error when creating the production directory in CI/CD
2024-07-18 Update build.yml
    Use upload-artifact v4
2024-07-18 Update build.yml
    Upgrade checkout to version 4
2024-07-20 Some position adjustments
2024-07-23 Upgrade to KiCAD v8, update dates in schematic and layout
2024-07-28 Add level shifter for RTC I2C, fix non ideal footprint for NTS0104GU12
2024-08-14 Swap DISPLAY-CLK and DISPLAY-DATA to optimize the routing
2024-08-15 Allow running workflows manually.
2024-08-24 Add LED as an option instead of the buzzer for the sensor board
2024-09-03 Update microfone footprint
2024-09-26 Fixes "Footprint library "F:/Git/ZSWatch-HW/project" not found error
    Simply changed the path to the project path using the corresponding variable.
2024-09-26 test
2024-09-26 fixed footprint path to use relative project path
2024-09-26 changed Textfields "Board Characterstics" and "Stack Up"-Table to be in english.
2024-09-26 i'm idiot.
    here we go again. i'm an idiot apperently.
2024-09-27 Fix wrong transistors for I2C level shifter
2024-09-28 Closes #68
2024-09-28 backup for the builder
2024-09-28 Update and rename build copy.yml to build2.yml
    first tryout
2024-09-28 Update build2.yml
    rename
2024-09-28 Update build2.yml
    updated workflow
2024-09-28 Update build2.yml
    minor change
2024-09-28 Update build2.yml
    workflow change
2024-09-28 Update build2.yml
    bugfix workflow
2024-09-28 Update build2.yml
    workflow test
2024-09-28 Update build2.yml
    kibot should use the right config
2024-09-28 Update zswatch.kibot.yaml
    added subdirectory.
2024-09-28 Update build2.yml
    removed whitespace
2024-09-28 Update build2.yml
    removed variants
2024-09-28 Update zswatch.kibot.yaml
    hopefully set an output dir for each variant
2024-09-28 Update zswatch.kibot.yaml
    still with the output...
2024-09-28 Update zswatch.kibot.yaml
    reversed changes
2024-09-28 Update build2.yml
    reversed changes
2024-09-28 Update build2.yml
    added again screenshot stuff.
2024-09-28 Update build2.yml
    fixed artifact upload
2024-09-29 Update build2.yml
    simplified action
2024-09-29 Update zswatch.kibot.yaml
    updated kibot.yaml config
2024-09-29 Update build2.yml
    further simplifcation of workflow
2024-09-29 Update build2.yml
    test
2024-09-29 Update build2.yml
    changed kibot.yaml path
2024-09-29 Update build2.yml
    removed cd into project folder
2024-09-29 Update zswatch.kibot.yaml
    revert changes
2024-09-29 Update build.yml
    Simplified action to generate files
2024-09-29 Delete .github/workflows/build2.yml
    removed this file, because it was just for testing
2024-09-29 Add missing schematics changes for level shifter mirroring
2024-09-30 Update build.yml
    simplified github action to generate the KiCAD output files.
2024-09-30 Revert "Merge branch 'main' of https://github.com/blubbsy/ZSWatch-HW"
    This reverts commit defd07d079a79b64ac2961d13251908a77462948, reversing
    changes made to 67b4a96c99577db0457afa0c02bb7202dbcb8efd.
    i'm idiot.
    here we go again. i'm an idiot apperently.
    backup for the builder
    Update and rename build copy.yml to build2.yml
2024-10-13 * added new library path (necessary?)
    * Added footprints from external library
    * Added Project relevant paths
    * Added 3D Models from external library
2024-10-13 * removed Bosch footprint that wasnt used at all (is in the LGA lib)
    * Changed path of 3D Models to use the prj path.
2024-10-18 Changed to project based libraries for the components
    * Extracted Kampis KiCAD library to convert it to a project library.
    * Did not seperated the LGA footprint/symbols from kampi. Not sure if this should be changed, but so far it works?
    * Had problems on another computer, because the 3D models were not loaded there, but on my other computer it works. Would be good to confirm that it works.
    * Cleaned-Up most of the not used footprints/symbols from the library. I think some of the bosch are still left, but i dont think that it is thaaaaaaat bad to keep them.
2024-10-24 Change layer for PCB tables to User1
2024-10-24 Added .gitignore for KiCAD
    used the template from https://github.com/github/gitignore/blob/main/KiCad.gitignore and removed the part for the BOM (wanted content).
    the rest ist probably not necessary at the moment. simply helps to keep everything cleaner without thinking :)
2024-10-24 just cleanup
2024-10-24 Remove accidentally added file.
2024-10-24 changed default library from KiCAD6 to KiCAD8
    changed default library from KiCAD6 to KiCAD8
2024-10-29 Rename signals and update symbols and footprints
2024-11-01 Overview page is now page number 1
2024-11-01 Add workflow to create diff for feature branches
2024-11-03 - Switch to a local KiCad library
2024-11-03 Rename Order. No. field in Order No.
2024-11-03 Add new vibration motor
2024-11-03 Fix wrong footprint path in symbols, add new vibration motor to PCB
2024-11-04 Display is now supplied with 3V0, add current consumption overview, vibration motor is now supplied with 3V0, add 0R series resistor for buzzer
2024-11-05 ci: Run CI on pull requests also.
2024-11-05 ci: Fix kidiff output resolution to a valid range.
2024-11-05 ci: Update uploaded artifact name in diff.yml
2024-11-05 ci: Add comment to PR with link do the Kidiff of the changes.
2024-11-05 Fix path to ci workflow READE badge.
2024-11-07 Fix cherry-pick conflict
2024-11-07 - Cherry picking commits from main - Update diff.yml - ci: Fix kidiff output resolution to a valid range. - ci: Update uploaded artifact name in diff.yml - Fix cherry-pick conflict - Fix path to ci w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
2024-11-07 Remove KiCad library from Kampi
2024-11-07 Remove dependencies step
2024-11-07 Remove update command
2024-11-07 Switch to KiBot container
2024-11-09 Fix different documentation issues
2024-11-23 CAD: Update to latest case files.
2024-12-08 Revert "* removed Bosch footprint that wasnt used at all (is in the LGA lib)"
    This reverts commit b7c6b640b3c77302b6ae9ae1867d90fe4c38a003.
2024-12-08 Revert "* added new library path (necessary?)"
    This reverts commit 9c7e5afd7c600660368f0d4d220e23e3204d2241.
2024-12-08 Revert "Revert "Merge branch 'main' of https://github.com/blubbsy/ZSWatch-HW""
    This reverts commit 854df55a28f7c5e6e02f69d8926a9c42906209c6.
2024-12-08 Add warning about development branch
2024-12-08 Fix patch for 3D model of nPM1300.
    Caused by renaming in Library repo.
2024-12-08 README: Add notes about release/development branch and production files.

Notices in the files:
README.md:
License: GPL 3.0
parts and their libraries:
Copyright 2021 Accelerated Designs. All rights reserved.
